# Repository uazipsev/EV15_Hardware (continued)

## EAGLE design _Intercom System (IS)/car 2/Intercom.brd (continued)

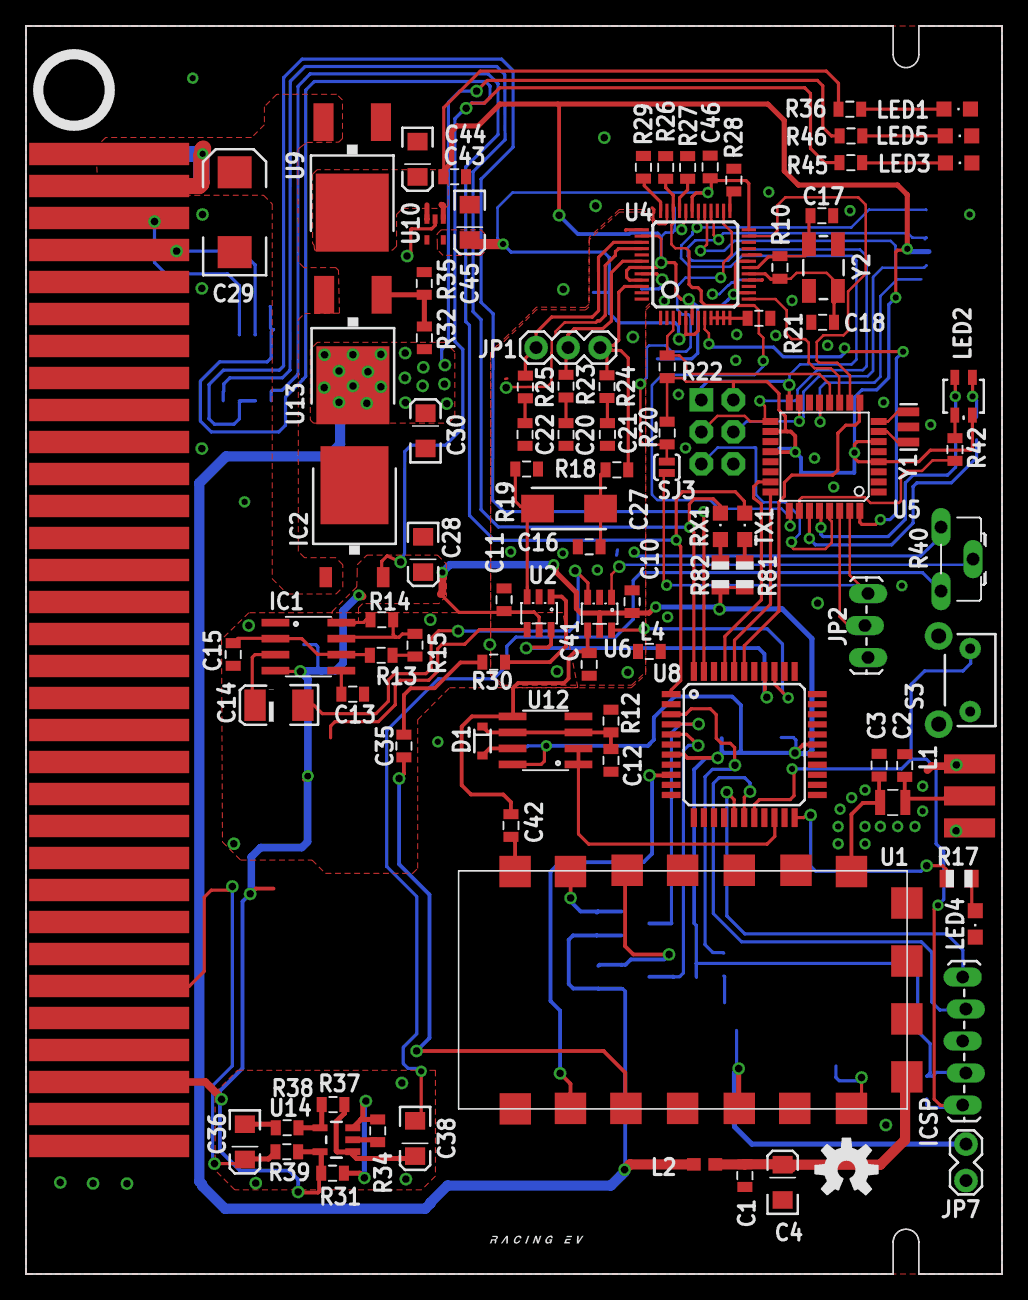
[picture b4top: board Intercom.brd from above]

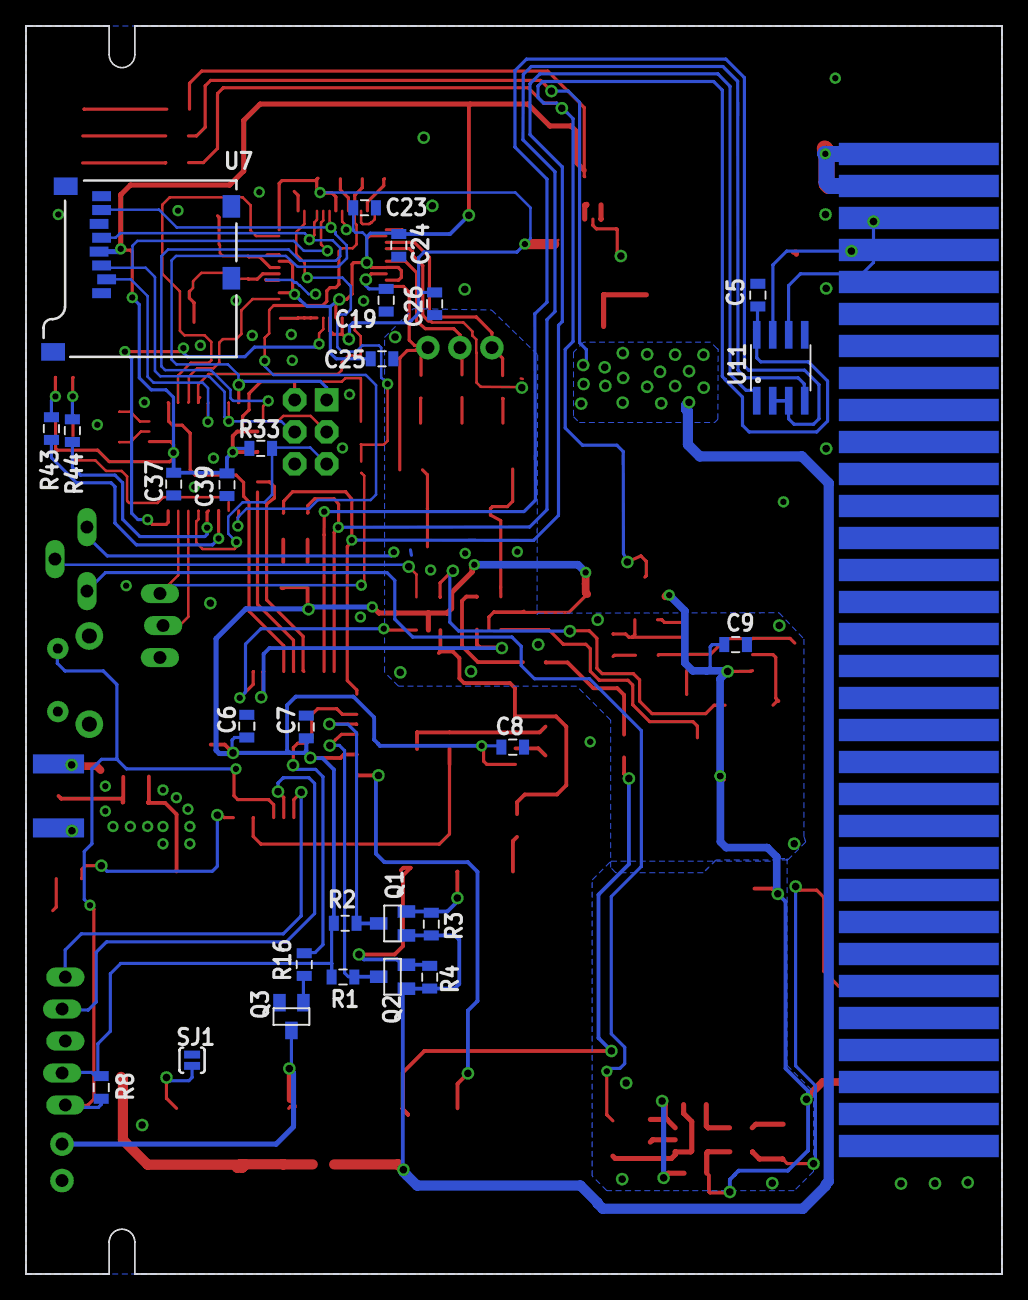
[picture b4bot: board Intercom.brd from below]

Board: 2 copper layers, 77.5 x 99.1 mm, 126 parts (27 on the bottom side), 97 nets.

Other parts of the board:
U$1: L-MS

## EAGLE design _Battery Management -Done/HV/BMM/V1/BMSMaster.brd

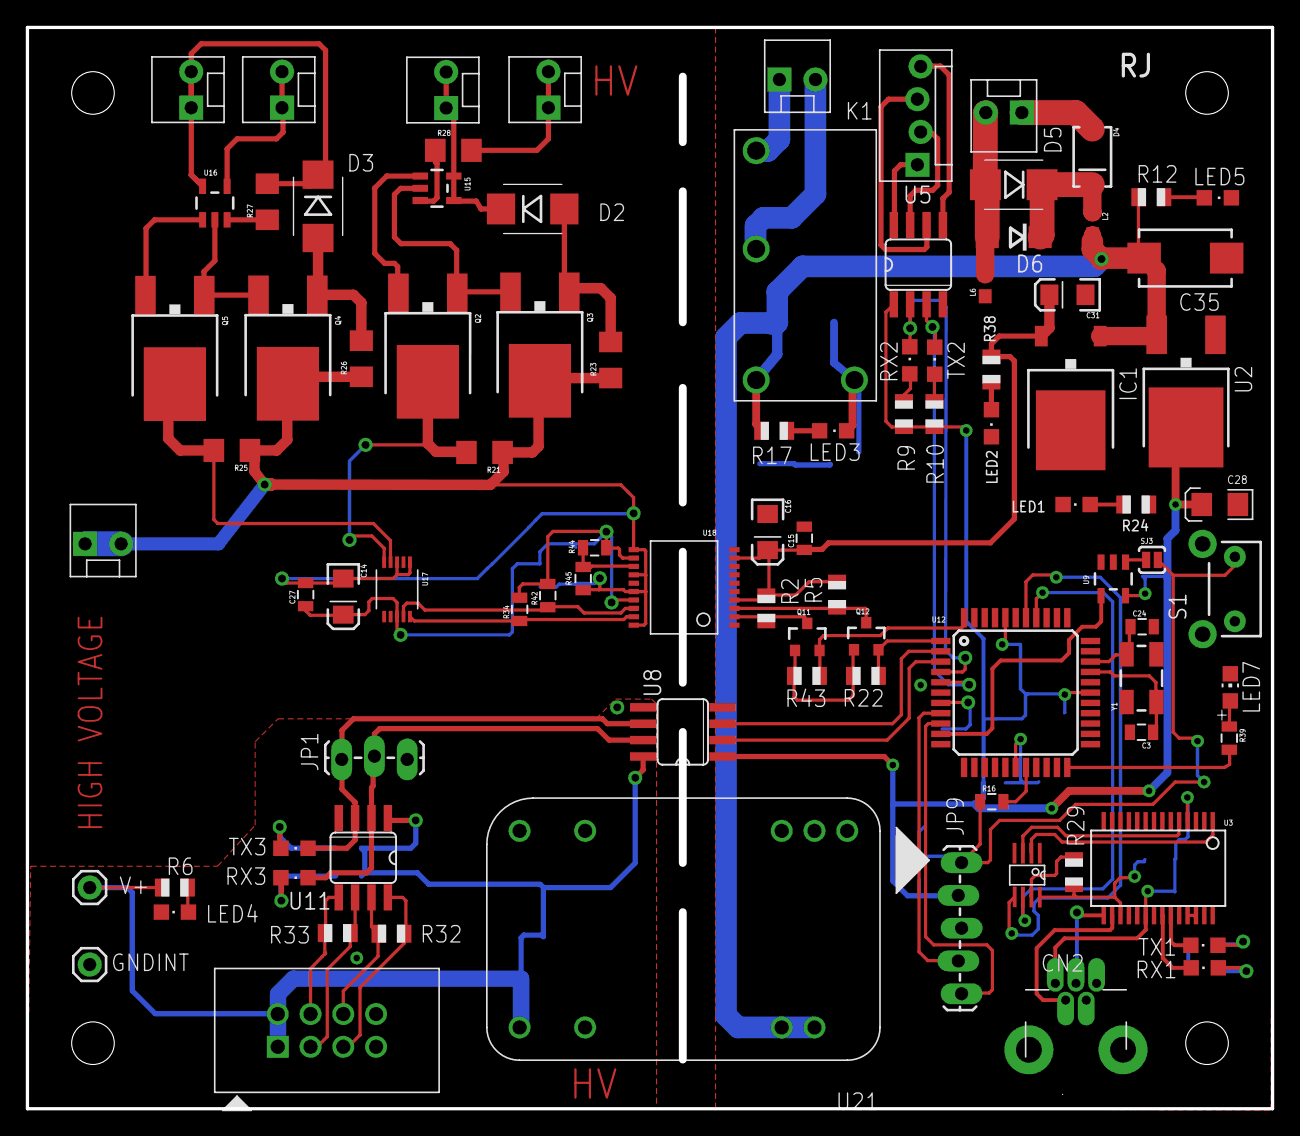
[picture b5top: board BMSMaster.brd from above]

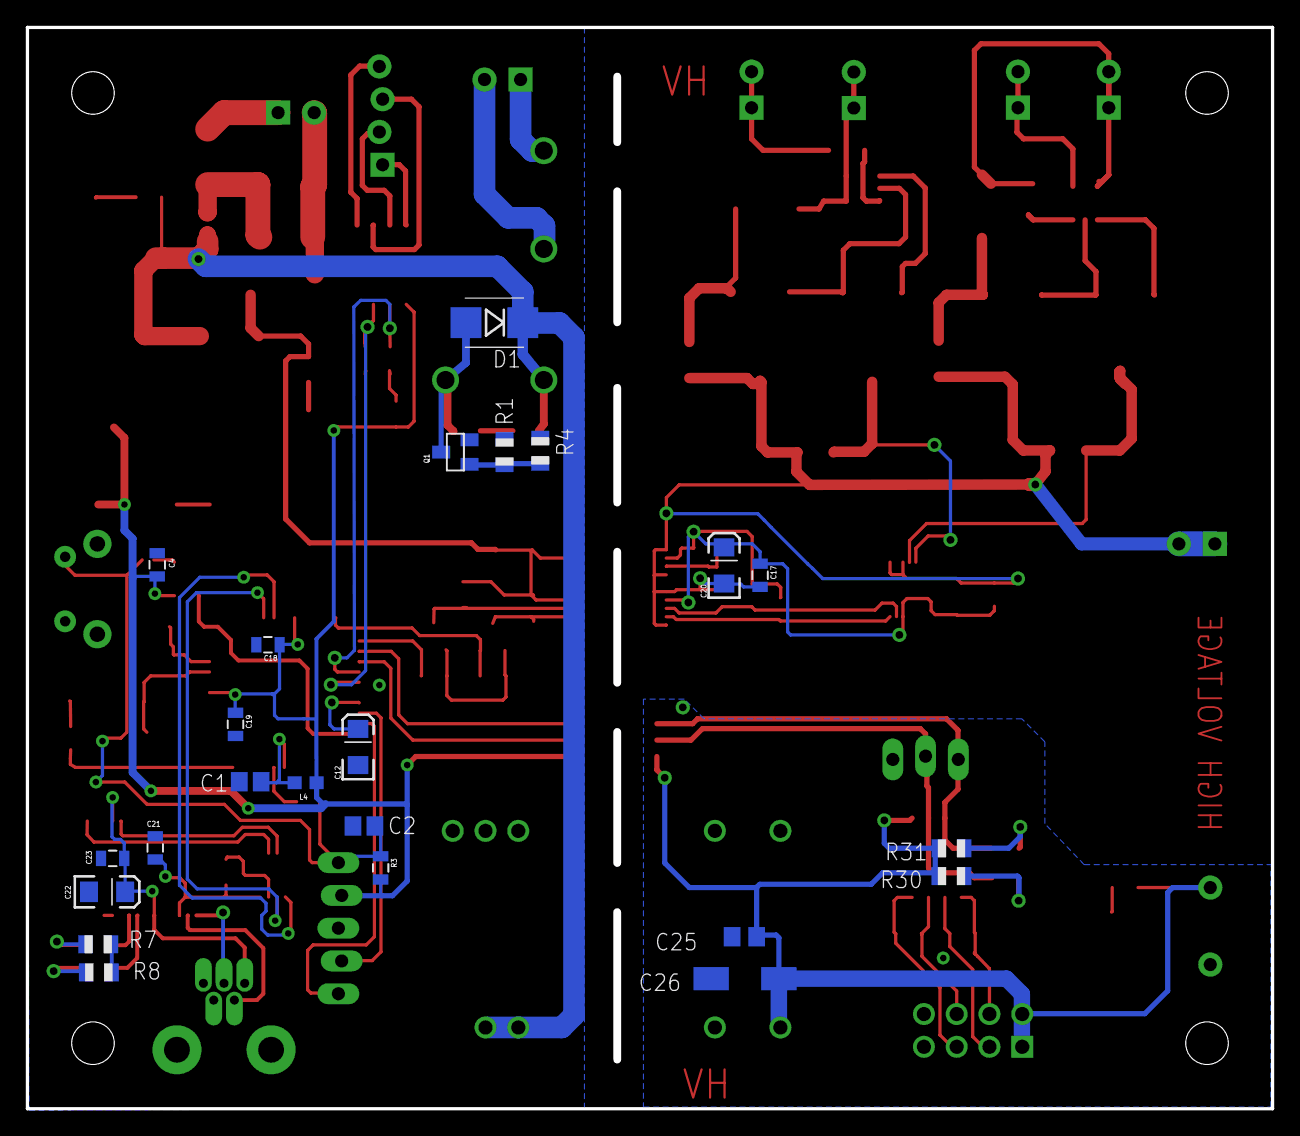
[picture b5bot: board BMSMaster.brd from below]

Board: 2 copper layers, 96.5 x 83.8 mm, 120 parts (23 on the bottom side), 85 nets.

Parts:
C1: 100n; C0805
C2: 10n; C0805
C3, C24: 12pF; 0805
C4, C21, C23: 0.1uf; 0805
C12, C14, C16, C20, C22, C31: 10uF; EIA3216
C15, C17, C18, C19, C27: 0.1uF; 0805
C25: 0.1uF; C0805
C26: 100uF; C/6032-28W
C28: 10uF; POLC1206
C35: 100uF; CT7343
CN2: USB-MINIB-THM-MOLEX
D1: SMB-DIODE
D2, D3: CMZ59448; DIODE-HV
D4: SMA-DIODE
D5: 14v; SMB-DIODE
D6: TVS; DO-214AC
GNDINT: M01PTH; 1X01
IC1: 7805DT; TO252
J2: M8; 75869-132LF
J4: MOLEX-1X4_LOCK
JP1: SLAVE-DEBUG; 1X03_LOCK_LONGPADS
JP2, JP6, JP10: BPACK; MOLEX-1X2_LOCK
JP3, JP4: M02POLAR_LOCK; MOLEX-1X2_LOCK
JP5, JP11: LOAD; MOLEX-1X2_LOCK
JP9: ICSP; 1X05_LOCK_LONGPADS
K1: ALQ312
L2, L6: FERITEBEAD; 0603
L4: FB; 0603
LED1, LED2, LED3, LED4, LED5: Green; CHIPLED_0805
LED7: CHIP-LED0805
Q1: NTR5198NLT1G; SOT23
Q2, Q3, Q4, Q5: FQD3P50; DPAK
Q11, Q12: BSS138; SOT23-3
R1: 100K; R0805
R2, R5, R22, R43: 2k; R0805
R3, R45: 10k; 0805
R4, R7, R9, R29, R30: 1K; R0805
R6, R8, R10, R31, R38: 1k; R0805
R12, R17: 3.3k; R0805
R16, R39: 499; 0805
R21, R25: 4.99k; 1206
R23, R26: 2M; 1206
R24: 499; R0805
R27, R28: 100; 1206
R32, R33: 120; R0805
R34, R42: 2k; 0805
R44: 30.6k; 0805
RX1: CHIPLED_0805
RX2, RX3: RED; CHIPLED_0805
S1: ts; TACTILE-PTH-SIDEEZ
SJ3: SJ-NO; SJ_2S-NO
STANDOFF1, STANDOFF2, STANDOFF3, STANDOFF4: STAND-OFF
TX1: CHIPLED_0805
TX2, TX3: GREEN; CHIPLED_0805
U2: V_REG_317DPACK; V-REG_DPACK
U3: FT232RL-BASICSSOP; SSOP28DB
U4: SN74LVC2G241DCTR; VFSOP-8
U5, U11: ISL83077; SO08
U8: ISO7221ADR; SOIC-8
U9: MAX823; SOT23-5L
U12: DSPIC33FJ128GP804; TQFP-44
U15, U16: LTC6101; SOT23-5
U17: ADS1015; MSOP-10
U18: ADM3260; SSOP-20
U21: REC7.5-1205SRW/H2/A/M; 24DIPMOD-8LEAD
U$1: INDPK1; PICKIT-PIN-1
V+: M01PTH; 1X01
Y1: 12Mhz; CRYSTAL-SMD-5X3

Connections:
3.3V: C4.1, C18.1, C19.1, C28.1, JP9.2, L4.2, R3.2, R9.2, R10.2, R24.2, U2.4, U5.1, U8.1, U9.5, U12.28, U12.40
3V: C21.1, R29.2, U3.17, U4.8
3V3SCL: Q11.2, R43.1, U12.44
3V3SDA: Q12.2, R22.1, U12.1
+3V3: Q11.1, Q12.1, R22.2, R43.2
+5V: C15.1, C16.A, C31.A, IC1.2, R2.2, R5.2, R38.2, U18.4, U18.9
+12V: C35.+, D1.C, IC1.1, K1.C1, L2.2, R12.2, R17.2, U2.3, U21.22, U21.23
BMS-RX: U8.2, U12.3
BMS-TX: U8.3, U12.2
CRNTA: Q2.2, R21.2, U17.5
CRNTB: Q5.2, R25.2, U17.4
GND: C1.2, C2.2, C3.2, C4.2, C12.C, C15.2, C16.C, C18.2, C19.2, C21.2, C22.C, C23.2, C24.2, C28.2, C31.C, C35.-, CN2.GND, IC1.3, JP9.3, L6.1, LED1.C, LED2.C, LED5.C, LED7.C, Q1.2, R1.1, S1.1, U2.1, U3.7, U3.18, U3.21, U3.25, U3.26, U4.1, U4.4, U5.4, U8.4, U9.2, U12.6, U12.16, U12.29, U12.39, U18.1, U18.5, U18.7, U18.10, U21.2, U21.3
GNDINT: C25.2, C26.-, GNDINT.1, J2.7, J2.8, JP1.1, LED4.C, U8.5, U11.4, U21.16
unnamed: LED7.A, R39.1
unnamed: C24.1, U12.31, Y1.3
unnamed: J4.4, U5.5
unnamed: C3.1, U12.30, Y1.1
unnamed: SJ3.1, U9.1
unnamed: CN2.D-, U3.16
unnamed: LED1.A, R24.1
unnamed: CN2.D+, U3.15
unnamed: LED5.A, R12.1
unnamed: R7.1, TX1.A
unnamed: J4.3, U5.6
unnamed: J4.2, U5.7
unnamed: J4.1, U5.8
unnamed: R8.1, RX1.A
unnamed: TX1.C, U3.23
unnamed: RX1.C, U3.22
unnamed: R10.1, TX2.A
unnamed: U3.1, U4.2
unnamed: JP3.2, K1.COM
unnamed: U3.5, U4.3
unnamed: C1.1, L4.1, U12.17
unnamed: LED2.A, R38.1
unnamed: JP3.1, K1.N.O
unnamed: D3.C, JP6.1, JP6.2, R27.2, U16.5
unnamed: J2.3, R33.2, U11.6
unnamed: C12.A, U12.7
unnamed: LED4.A, R6.2
unnamed: JP5.1, JP5.2, R28.2
unnamed: D1.A, K1.C2, LED3.C, Q1.3
unnamed: Q1.1, R1.2, R4.1
unnamed: R9.1, RX2.A
unnamed: J2.4, R33.1, U11.5
unnamed: J2.5, R32.1, U11.8
unnamed: J2.6, R32.2, U11.7
unnamed: R39.2, U12.22
unnamed: C2.1, JP9.1, R3.1, R16.1, S1.2, SJ3.2
unnamed: R16.2, U12.18
unnamed: JP9.4, U12.8
unnamed: JP9.5, U12.9
unnamed: LED3.A, R17.1
unnamed: D2.C, JP10.1, JP10.2, U15.4, U15.5
unnamed: D3.A, Q4.1, R26.2
unnamed: C14.A, C17.1, C20.A, C27.1, R34.2, R42.2, R44.2, U17.8, U18.12, U18.17
unnamed: JP11.1, JP11.2, U16.4
unnamed: D2.A, Q3.1, R23.2
unnamed: R34.1, U17.10, U18.19
unnamed: R27.1, U16.3
unnamed: Q2.1, Q3.3, U15.2
unnamed: Q2.3, U15.1
unnamed: Q5.3, U16.1
unnamed: Q4.3, Q5.1, U16.2
unnamed: R28.1, U15.3
unnamed: R42.1, U17.9, U18.18
unnamed: R44.1, R45.2, U18.13
unnamed: R29.1, U4.7
unnamed: R30.1, RX3.A
unnamed: R31.1, TX3.A
unnamed: C22.A, C23.1, CN2.VBUS, R7.2, R8.2, U3.4, U3.20
unnamed: D5.A, D6.A, JP4.2, L6.2
unnamed: D4.A, JP4.1
unnamed: D4.C, D5.C, D6.C, L2.1
PIC1: JP1.2, RX3.C, U8.7, U11.2
PIC2: JP1.3, TX3.C, U8.6, U11.3
RX2: RX2.C, U5.2, U12.4
RX3: U4.6, U12.37
SCL: Q11.3, R2.1, U18.2
SDA: Q12.3, R5.1, U18.3
TX2: TX2.C, U5.3, U12.5
TX3: U4.5, U12.38
V+: C25.1, C26.+, J2.1, J2.2, R6.1, R30.2, R31.2, U8.8, U11.1, U21.14, V+.1
V-: C14.C, C17.2, C20.C, C27.2, JP2.1, JP2.2, Q3.2, Q4.2, R21.1, R23.1, R25.1, R26.1, R45.1, U17.1, U17.3, U18.11, U18.14, U18.16, U18.20
WDI: U9.4, U12.10

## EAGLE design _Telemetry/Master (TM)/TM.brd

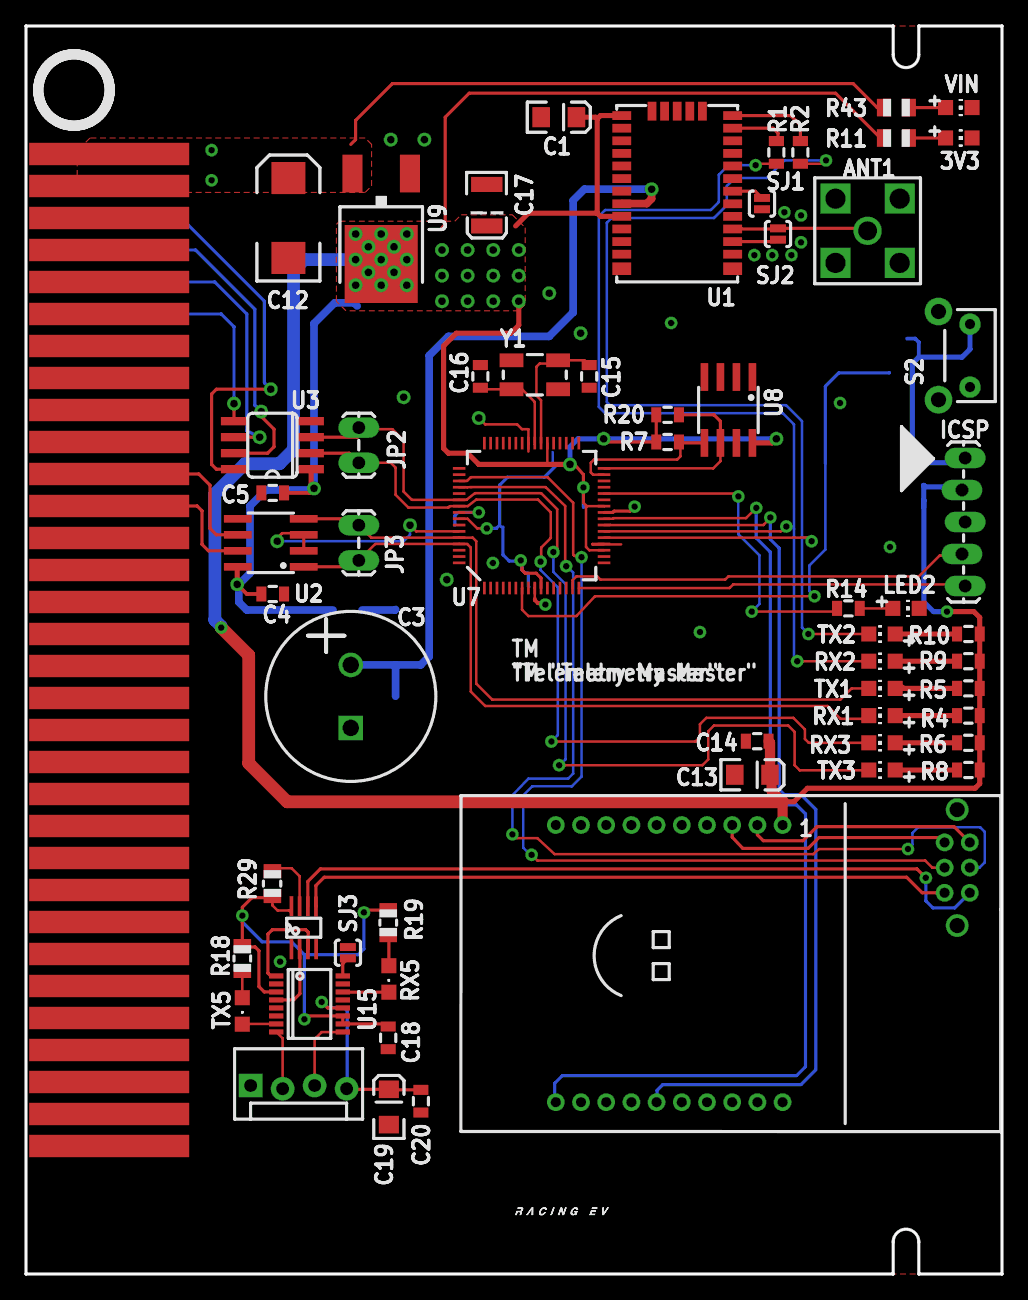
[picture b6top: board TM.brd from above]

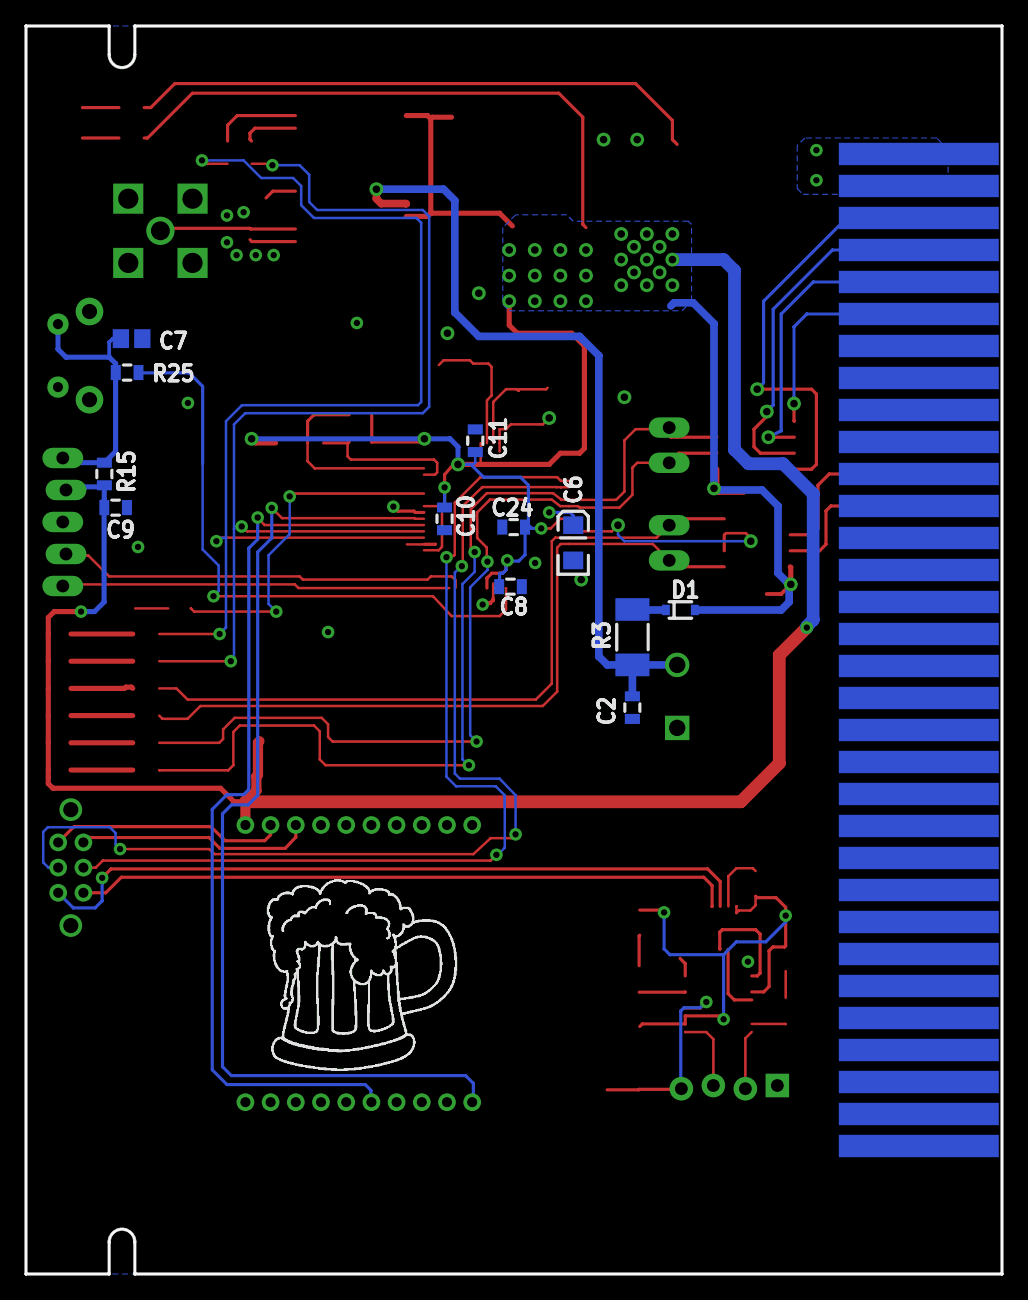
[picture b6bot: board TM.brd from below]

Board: 2 copper layers, 77.5 x 99.1 mm, 76 parts (13 on the bottom side), 62 nets.

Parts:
3V3: CHIP-LED0805
ANT1: CONMCX002; CONSMA002
C1, C6, C13: 10uF; EIA3216
C2, C14: 1uF; 0805
C3: DB-5R5D224T
C4, C5, C8, C9, C10, C11, C24: 0.1uF; 0805
C7: 10n; C0805
C12: 10uF; EIA7343
C15, C16: 12pF; 0805
C17: 10uf; EIA3528
C18, C20: 0.1uf; 0805
C19: 4.7uF; EIA3216
CARD2: CARD; CARD-64
D1: BAS316-TP; SOD-323
ICSP: ICSP; 1X05_LOCK_LONGPADS
JP2, JP3: M02LOCK_LONGPADS; 1X02_LOCK_LONGPADS
JP13: MOLEX-1X4_LOCK
LED2: CHIP-LED0805
R1, R2: 220; 0805
R3: 50; R2010
R4, R5, R6, R8, R9, R10: 1k; 0805
R7, R20: 2k; 0805
R11: 499; R0805
R14, R25: 499; 0805
R15: 10k; 0805
R18, R29: 1K; R0805
R19, R43: 1k; R0805
RX1, RX2, RX3: CHIP-LED0805
RX5: CHIPLED_0805
S1: EG2211
S2: ts; TACTILE-PTH-SIDEEZ
SJ1, SJ2: NO; SJ_2S-NO
SJ3: PAD-JUMPER-2-NO_YES_SILK
TX1, TX2, TX3: CHIP-LED0805
TX5: CHIPLED_0805
U1: CAM-M8Q
U2: SN75HVD08DR; SO-8
U3: ISL83077; SO08
U4: SN74LVC2G241DCTR; VFSOP-8
U5: RM024; RM024-TH
U7: DSPIC33EP256GM306; TQFP-64
U8: CAT24M01WI-GT3; SO08
U9: NCP1117DT33T5G; V-REG_DPACK
U15: FT230X; SSOP-16
U$1: BEERM; B-M
U$2: LOGO; L-MS
U$3: INDPK1; PICKIT-PIN-1
VIN: CHIP-LED0805
Y1: 12Mhz; CRYSTAL-SMD-5X3

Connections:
3V: C18.1, R18.2, R19.2, R29.2, U4.8, U15.3, U15.10, U15.11
+3V3: C1.A, C4.1, C5.1, C8.1, C9.1, C10.1, C11.2, C13.A, C14.1, C17.A, C24.1, D1.2, ICSP.2, R4.1, R5.1, R6.1, R7.2, R8.1, R9.1, R10.1, R11.2, R15.2, R20.2, U1.1, U1.9, U2.8, U3.1, U5.1, U7.10, U7.19, U7.26, U7.38, U7.57, U8.8, U9.4
+9V: C12.A, CARD2.1, CARD2.2, CARD2.33, CARD2.34, R43.2, U9.3
CONNECTED: U5.15, U7.23
GND: 3V3.C, ANT1.1, ANT1.2, ANT1.3, ANT1.4, C1.C, C2.2, C3.-, C4.2, C5.2, C6.C, C7.2, C8.2, C9.2, C10.2, C11.1, C12.C, C13.C, C14.2, C15.2, C16.2, C17.C, C18.2, C19.C, C20.2, C24.2, CARD2.31, CARD2.32, CARD2.63, CARD2.64, ICSP.3, JP13.1, LED2.C, S2.1, SJ1.1, SJ3.1, U1.4, U1.5, U1.10, U1.11, U1.12, U1.13, U1.14, U1.15, U1.18, U1.19, U1.21, U1.22, U1.27, U1.31, U2.5, U3.4, U4.1, U4.4, U5.10, U7.9, U7.20, U7.25, U7.41, U8.1, U8.2, U8.3, U8.4, U8.7, U9.1, U15.5, U15.13, VIN.C
GPS-RX: R2.2, TX2.C, U7.21
GPS-TX: R1.2, RX2.C, U7.22
unnamed: R9.2, RX2.A
unnamed: R1.1, U1.25
unnamed: ANT1.C, SJ2.2, U1.17
unnamed: R2.1, U1.26
unnamed: SJ1.2, U1.20
unnamed: D1.1, R3.2
unnamed: 3V3.A, R11.1
unnamed: C2.1, C3.+, R3.1, U1.8
unnamed: R6.2, RX3.A
unnamed: R8.2, TX3.A
unnamed: R18.1, TX5.A
unnamed: R14.2, U7.28
unnamed: C16.1, U7.40, Y1.3
unnamed: C15.1, U7.39, Y1.1
unnamed: LED2.A, R14.1
unnamed: R7.1, U7.31, U8.5
unnamed: SJ2.1, U1.16
unnamed: R19.1, RX5.A
unnamed: TX5.C, U15.7
unnamed: RX5.C, U15.14
unnamed: U4.2, U15.4
unnamed: R4.2, RX1.A
unnamed: R5.2, TX1.A
unnamed: R10.2, TX2.A
unnamed: U4.3, U15.1
unnamed: JP13.3, U15.9
unnamed: R20.1, U7.32, U8.6
unnamed: R43.1, VIN.A
unnamed: JP13.2, U15.8
unnamed: SJ3.2, U15.16
unnamed: R29.1, U4.7
unnamed: C19.A, C20.1, JP13.4, U15.12
unnamed: C7.1, ICSP.1, R15.1, R25.1, S2.2
unnamed: R25.2, U7.7
unnamed: C6.A, U7.56
unnamed: ICSP.4, U7.15
unnamed: ICSP.5, U7.16
RS-TM-A: CARD2.35, U3.8
RS-TM-B: CARD2.36, U3.7
RS-TM-Y: CARD2.38, U3.5
RS-TM-Z: CARD2.37, U3.6
RX: S1.P1, U7.52
RXD0: JP3.2, RX1.C, U2.1, U7.61
RXD2: JP2.2, RX3.C, U3.2, U7.55
RXD3: S1.P1-TA, U4.6
RXD4: S1.P1-TB, U5.2
SETUP: U5.11, U7.24
TSA: CARD2.11, U2.6
TSB: CARD2.12, U2.7
TX: S1.P2, U7.51
TXD0: JP3.1, TX1.C, U2.4, U7.60
TXD2: JP2.1, TX3.C, U3.3, U7.54
TXD3: S1.P2-TA, U4.5
TXD4: S1.P2-TB, U5.3
U3-EN: U2.2, U2.3, U7.59

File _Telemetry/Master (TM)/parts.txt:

Partlist

Exported from TM.brd at 9/13/2015 10:17:09 AM

EAGLE Version 6.6.0 Copyright (c) 1988-2014 CadSoft

Assembly variant: 

Part     Value             Package                  Library                    Position (mil)        Orientation

3V3                        CHIP-LED0805             adafruit                   (2915 3550)           R270
ANT1     CONMCX002         CONSMA002                FSAE Eletric               (2630 3260)           R0
C1       10uF              EIA3216                  SparkFun-Passives          (1665 3615)           R0
C2       1uF               0805                     SparkFun-Passives          (1155 1770)           MR270
C3       DB-5R5D224T       DB-5R5D224T              FSAE Eletric               (1015 1805)           R90
C4       0.1uF             0805                     SparkFun-Capacitors        (771 2125)            R0
C5       0.1uF             0805                     SparkFun-Capacitors        (771 2441)            R180
C6       10uF              EIA3216                  SparkFun-Capacitors        (1340 2285)           MR90
C7       10n               C0805                    adafruit                   (2720 2923)           MR0
C8       0.1uF             0805                     SparkFun-Capacitors        (1536 2148)           MR0
C9       0.1uF             0805                     SparkFun-Capacitors        (2770 2395)           MR0
C10      0.1uF             0805                     SparkFun-Capacitors        (1742 2360)           MR270
C11      0.1uF             0805                     SparkFun-Capacitors        (1646 2604)           MR270
C12      10uF              EIA7343                  SparkFun-Capacitors        (820 3300)            R90
C13      10uF              EIA3216                  SparkFun-Passives          (2270 1560)           R0
C14      1uF               0805                     SparkFun-Passives          (2285 1665)           R180
C15      12pF              0805                     SparkFun-Capacitors        (1760 2805)           R270
C16      12pF              0805                     SparkFun-Capacitors        (1420 2805)           R90
C17      10uf              EIA3528                  SparkFun-Capacitors        (1440 3340)           R270
C18      0.1uf             0805                     SparkFun                   (1132 738)            R270
C19      4.7uF             EIA3216                  SparkFun                   (1134 522)            R90
C20      0.1uf             0805                     SparkFun                   (1234 540)            R270
C24      0.1uF             0805                     SparkFun-Capacitors        (1526 2334)           MR180
CARD2    CARD              CARD-64                  FSAE Eletric               (0 3900)              R270
D1       BAS316-TP         SOD-323                  SparkFun-DiscreteSemi      (1005 2075)           MR0
ICSP     ICSP              1X05_LOCK_LONGPADS       SparkFun-Connectors        (2935 2550)           R270
JP2      M02LOCK_LONGPADS  1X02_LOCK_LONGPADS       SparkFun-Connectors        (1040 2640)           R270
JP3      M02LOCK_LONGPADS  1X02_LOCK_LONGPADS       SparkFun-Connectors        (1040 2335)           R270
JP13                       MOLEX-1X4_LOCK           SparkFun-Connectors        (702 584)             R0
LED2                       CHIP-LED0805             adafruit                   (2750 2080)           R270
R1       220               0805                     SparkFun-Passives          (2345 3505)           R270
R2       220               0805                     SparkFun-Passives          (2420 3505)           R270
R3       50                R2010                    SparkFun-Passives          (1155 1990)           MR90
R4       1k                0805                     SparkFun-Passives          (2945 1745)           R180
R5       1k                0805                     SparkFun-Passives          (2945 1830)           R180
R6       1k                0805                     SparkFun-Passives          (2945 1660)           R180
R7       2k                0805                     SparkFun-Passives          (2005 2600)           R180
R8       1k                0805                     SparkFun-Passives          (2945 1575)           R180
R9       1k                0805                     SparkFun-Passives          (2945 1915)           R180
R10      1k                0805                     SparkFun-Passives          (2945 2000)           R180
R11      499               R0805                    adafruit                   (2720 3550)           R180
R14      499               0805                     SparkFun-Passives          (2570 2080)           R180
R15      10k               0805                     SparkFun-Passives          (2805 2500)           MR270
R18      1K                R0805                    adafruit                   (676 986)             R90
R19      1k                R0805                    adafruit                   (1132 1098)           R90
R20      2k                0805                     SparkFun-Passives          (2005 2685)           R180
R25      499               0805                     SparkFun-Resistors         (2734 2817)           MR0
R29      1K                R0805                    adafruit                   (770 1220)            R270
R43      1k                R0805                    adafruit                   (2720 3645)           R180
RX1                        CHIP-LED0805             adafruit                   (2675 1745)           R90
RX2                        CHIP-LED0805             adafruit                   (2675 1915)           R90
RX3                        CHIP-LED0805             adafruit                   (2675 1660)           R90
RX5                        CHIPLED_0805             adafruit                   (1134 922)            R180
S1                         EG2211                   SparkFun-Electromechanical (2910 1270)           R180
S2       ts                TACTILE-PTH-SIDEEZ       SparkFun-Electromechanical (2950 2870)           R90
SJ1      NO                SJ_2S-NO                 SparkFun-Passives          (2300 3345)           R90
SJ2      NO                SJ_2S-NO                 SparkFun-Passives          (2350 3250)           R90
SJ3                        PAD-JUMPER-2-NO_YES_SILK SparkFun-Passives          (1006 1004)           R270
TX1                        CHIP-LED0805             adafruit                   (2675 1830)           R90
TX2                        CHIP-LED0805             adafruit                   (2675 2000)           R90
TX3                        CHIP-LED0805             adafruit                   (2675 1575)           R90
TX5                        CHIPLED_0805             adafruit                   (676 822)             R180
U1       CAM-M8Q           CAM-M8Q                  FSAE Eletric               (2035 3620)           R180
U2       SN75HVD08DR       SO-8                     FSAE Eletric               (765 2285)            R90
U3       ISL83077          SO08                     NASA_LIB                   (770 2590)            R90
U4       SN74LVC2G241DCTR  VFSOP-8                  Cleaverbrooks              (868 1082)            R0
U5       RM024             RM024-TH                 FSAE Eletric               (2010 970)            R0
U7       DSPIC33EP256GM306 TQFP-64                  FSAE Eletric               (1580 2370)           R0
U8       CAT24M01WI-GT3    SO08                     SparkFun-DigitalIC         (2195 2700)           R180
U9       NCP1117DT33T5G    V-REG_DPACK              SparkFun-PowerIC           (1110 3250)           R180
U15      FT230X            SSOP-16                  FSAE Eletric               (886 844)             R270
VIN                        CHIP-LED0805             adafruit                   (2915 3645)           R270
Y1       12Mhz             CRYSTAL-SMD-5X3          SparkFun-FreqCtrl          (1590 2810)           R180
